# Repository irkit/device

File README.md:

IRKit Device
===

IRKit device and [IRKit SDK](https://github.com/irkit/ios-sdk) lets you control your home electronics from your iOS and Android devices.
IRKit device has a Infrared LED and receiver, and a WiFi module inside.
Internet connected devices can make IRKit send IR signals for you.

## Get IRKit Device

In Japan: [amazon.co.jp](http://www.amazon.co.jp/gp/product/B00H91KK26)  
World wide shipping available: [switch-science](https://international.switch-science.com/catalog/1644/)

## Schematics

Basically, it's a [Arduino Leonardo](http://arduino.cc/en/Main/ArduinoBoardLeonardo) fork with following modifications:

* added a [WiFi module](http://www.gainspan.com/gs1011mips) ( [GainSpan](http://www.gainspan.com/home) 's WiFi module ).
* added Infrared Receiver, Infrared LED and some LEDs.

## Firmware

It's basically a normal Arduino sketch.

See [IRKit.ino](https://github.com/irkit/device/blob/master/firmware/src/IRKit/IRKit.ino)

## Board

### Top

### Bottom

## Case

See [Case](https://github.com/irkit/device/tree/master/case)

## Extend it!

Following Arduino pins are pulled out for you.

* D2,D3,D4,D5,D12,TXLED
* A0,A1,A2,A3

See [IRKit.sch, eagle schematic file](https://github.com/irkit/device/blob/master/hardware/IRKit.sch) 's CN2

## How to update firmware

You can use [Arduino IDE](http://arduino.cc/en/Main/Software) to write IRKit's firmware.  
Follow this procedure (for MacOS).

1. Download, install and run [Arduino IDE](http://arduino.cc/en/Main/Software)
1. Connect IRKit using USB Micro-B cable to Mac.
1. Navigate to Arduino IDE Menu and select Tools -> Board -> "Arduino Leonardo".
1. Navigate to Arduino IDE Menu and select Tools -> Serial Port -> "/dev/tty.usbmodemXXXX".

   XXXX part should differ on your environment.

1. Download latest zip file from [IRKit device tags](https://github.com/irkit/device/releases).
1. Unzip it and open `firmware/src/IRKit/` directory.
1. Rename `version.template` to `version.c` .

   FYI. Product version is embedded here in official builds.

1. Double click `IRKit.ino` in the same directory.
1. Navigate to Arduino IDE Menu and click File -> Upload, to write into IRKit.
1. All Done!

### Example fork of IRKit firmware

[@acourreges](https://github.com/acourreges) created a branch [settings-led-cloud](https://github.com/acourreges/device/tree/settings-led-cloud/firmware) that enables you to configure:  
* Status LED behaviour (you might want to turn the LED off when the device is idle?)
* Enable/Disable cloud control (you might want IRKit not to connect to Internet?)

See [config.h](https://github.com/acourreges/device/blob/settings-led-cloud/firmware/src/IRKit/config.h) for details.

## How to get logs

IRKit logs what it's doing to USB serial, and you can use [Arduino IDE](http://arduino.cc/en/Main/Software) to see it.  
Follow this procedure (for MacOS).

1. Download, install and run [Arduino IDE](http://arduino.cc/en/Main/Software)
1. Connect IRKit using USB Micro-B cable to Mac.
1. Navigate to Arduino IDE Menu and select Tools -> Serial Port -> "/dev/tty.usbmodemXXXX".

   XXXX part should differ on your environment.

1. Navigate to Arduino IDE Menu and select Tools -> Serial Monitor.
1. Change new window's right-bottom settings to "No line ending" and "115200 baud", and close the window.
1. Reconnect IRKit and immediately start Serial Monitor again.

   This is to collect logs as soon as IRKit startups.

1. Copy and send logs to IRKit developer, thanks!

## ファームウェアアップデート方法

IRKitのファームウェアは、 [Arduino IDE](http://arduino.cc/en/Main/Software) を使って書き込むことができます。

出荷時のファームウェアバージョンによって、どのファームウェアバージョンまでアップデートできるかが変わります。  
以下の手順で現在のバージョンを確認し、対応するバージョンを使用してください。

| 現在のバージョン | 対応する最新のバージョン |
| --- | --- |
| 1.3.3以下 | [1.3.3](https://github.com/irkit/device/releases/tag/v1.3.3) |
| 1.3.4以上 | [最新](https://github.com/irkit/device/releases/latest) |

[IRKitシンプルリモコン](https://itunes.apple.com/us/app/irkit-simple-remote/id778790928?l=ja&ls=1&mt=8) を起動し、左上のボタンから設定画面を開くと、以下の画像の赤の四角のようにファームウェアバージョンを表示します。

以下がファームウェアのアップデート方法です(MacOS編)。

1. [Arduino IDE](http://arduino.cc/en/Main/Software) をダウンロードしてインストール後、起動します。
1. IRKitをUSB Micro-Bケーブルを使ってMacに接続します。
1. Arduino IDEのメニューから ツール -> マイコンボード -> "Arduino Leonardo" を選びます。
1. Arduino IDEのメニューから ツール -> シリアルポート -> "/dev/tty.usbmodemXXXX" を選びます。

   環境によってXXXXの部分やその前後が異なる場合があります。

1. ファームウェアをダウンロードし、zipファイルを解凍します。
1. 解凍したディレクトリ内にある `firmware/src/IRKit/` ディレクトリを開きます。
1. 同ディレクトリ内の `version.template` を `version.c` にリネームします。  

   参考) 製品版ではIRKitのバージョン情報をここに埋め込んでいます。

1. 同ディレクトリ内の `GSwifi.cpp` 内に埋め込んであるWi-Fiアクセスポイントのパスワードを書き換えます。  

   https://github.com/irkit/device/blob/master/firmware/src/IRKit/GSwifi.cpp#L1096  
   の `XXXXXXXXXX` を任意の文字列に書き換えてください。  
   参考) IRKitの出荷前に書き換えてから出荷しています。

1. 同ディレクトリ内の `IRKit.ino` をダブルクリックして Arduino IDE で開きます。
1. Arduino IDEのメニューから ファイル -> マイコンボードに書き込む を押してIRKitに書き込みます。
1. 完了！

### プログラムメモリについて

IRKitのマイコン ATmega32U4 はプログラムメモリを 32kB 積んでいますが、  
IRKitのファームウェアでそのほぼ全てを使用しています。

ファームウェアに改造を行い、機能追加する場合には、  
不必要な機能のログ出力や機能自体を削ってください。

[log.hの22-26行目](https://github.com/irkit/device/blob/master/firmware/src/IRKit/log.h#L22) 辺りをコメントアウトすることで、ログ出力を止めることができます。

### IRKitファームウェアのFork例

[@acourreges](https://github.com/acourreges)の[settings-led-cloud](https://github.com/acourreges/device/tree/settings-led-cloud/firmware)では、以下を変更可能にしています。  
* ステータスLEDの動作 (赤外線を送受信していない時にはLEDを消灯しておきたい??)
* クラウドとの接続を有効/無効 (IRKitをインターネットに接続せずに使いたい??)

詳しくは [config.h](https://github.com/acourreges/device/blob/settings-led-cloud/firmware/src/IRKit/config.h) を見てください。

[@shokai](https://github.com/shokai)の[tempe_sensor](https://github.com/shokai/irkit-device/compare/master...tempe_sensor)ブランチ、[sensors_json](https://github.com/shokai/irkit-device/compare/master...sensors_json)ブランチでは、  
温度センサからの入力、アナログピンの値を読み、IRKit内蔵のWebサーバからHTTP GETで取得できるようにしています。

詳しくは [IRKitのファームウェアを改造して温度センサーを追加した](http://shokai.org/blog/archives/8802) をご覧ください。

## ログ取得方法

IRKitは、USB Micro-Bを使いパソコンまたはMacに接続すると、動作ログを取得することができます。  
以下の手順でログを取得します(MacOS編)。

1. [Arduino IDE](http://arduino.cc/en/Main/Software) をダウンロードしてインストール後、起動します。
1. IRKitをUSB Micro-Bケーブルを使ってMacに接続します。
1. Arduino IDEのメニューから ツール -> シリアルポート -> "/dev/tty.usbmodemXXXX" を選びます。

   環境によってXXXXの部分やその前後が異なる場合があります。

1. Arduino IDEのメニューから ツール -> シリアルモニタ を選びます。
1. 新しく開いたウィンドウの右下の設定を "改行なし" "115200baud" に変更し、一度ウィンドウを閉じます。
1. IRKitのUSB Micro-Bケーブルを外し、再度接続した直後に、上記同様に シリアルモニタ を開きます。

   IRKit起動直後からのログを取得するためです。

1. ウィンドウに表示される文字列をコピーして開発者へメールしてください。ありがとうございます！

## License

Firmware is licensed under GPLv2 or later.  
See details in [firmware/LICENSE](https://github.com/irkit/device/blob/master/firmware/LICENSE).

Schematics are licensed under Creative Commons Attribution Share-Alike license.  
See details in [hardware/LICENSE](https://github.com/irkit/device/blob/master/hardware/LICENSE).

Case is licensed under Creative Commons Attribution NonCommercial Share-Alike license.  
See details in [case/LICENSE](https://github.com/irkit/device/blob/master/case/LICENSE).

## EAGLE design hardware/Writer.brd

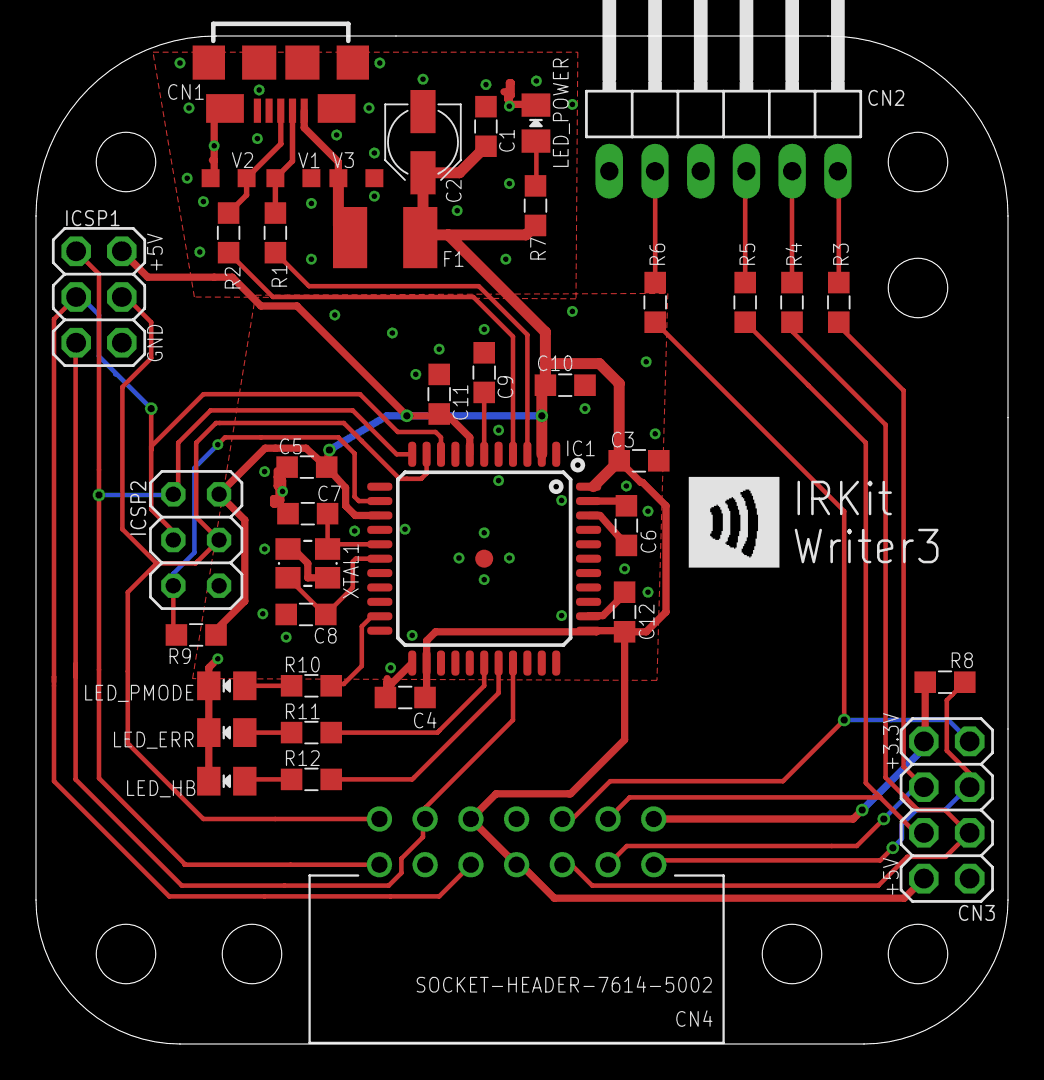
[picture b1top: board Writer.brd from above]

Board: 2 copper layers, 54.0 x 56.0 mm, 52 parts (0 on the bottom side), 33 nets.

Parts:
C1, C3, C4, C5, C6, C10, C11, C12: 0.1uF; SMD2012
C2: 10uF; PANASONIC_B
C7, C8: 12pF; SMD2012
C9: 1uF; SMD2012
CN1: ZX62-B-5PA(11); USB-MICROB
CN2: TTL-232R-3V3; 1X06/90
CN3: WiFi-Header; 2X04/D1.1
CN4: SOCKET-HEADER-7614-5002
F1: MF-MSMF075-2; L1812
IC1: ATMEGA32U4AU; TQFP44-PAD
ICSP1: IRKit ICSP; 2X03/D1.1
ICSP2: Writer ICSP; 2X03
LED_ERR: LED2012
LED_HB: LED2012
LED_PMODE: LED2012
LED_POWER: OSG50805C1C; LED2012
R1, R2: 22; SMD2012
R3, R4, R5, R6, R8: 1k; SMD2012
R7, R10, R11, R12: 5.1k; SMD2012
R9: 10k; SMD2012
SCREW1, SCREW2, SCREW3, SCREW4: flat-head M3 self-tapping; SCREW-M3
STANDOFF1, STANDOFF2, STANDOFF3, STANDOFF4, STANDOFF5, STANDOFF6, STANDOFF7: STAND-OFF
U$1: IRKIT-LOGO
V1, V2, V3: CG0603MLC-05E; CT/CN0603
XTAL1: 16MHz CL:10pF; CRYSTAL-3.2-2.5

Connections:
+3V3: CN3.1, CN4.2, R8.2
+5V: C1.1, C2.+, C3.2, C4.2, C5.2, C10.2, C11.2, C12.2, CN3.7, CN4.7, CN4.10, F1.2, IC1.2, IC1.7, IC1.14, IC1.24, IC1.34, IC1.44, ICSP1.2, ICSP2.2, R7.1, R9.2
AREF: C6.2, IC1.42
CTS#: CN2.2, R6.1
D1/LED_PMODE: IC1.21, R10.1
D8/LED_ERR: IC1.28, R11.1
D9/LED_HB: IC1.29, R12.1
GND: C1.2, C2.-, C3.1, C4.1, C5.1, C6.1, C7.1, C8.1, C9.1, C10.1, C11.1, C12.1, CN1.P5, CN1.S1, CN1.S2, CN1.S3, CN1.S4, CN1.S5, CN1.S6, CN2.1, CN3.8, CN4.8, CN4.11, IC1.5, IC1.15, IC1.23, IC1.35, IC1.43, IC1.P$1, ICSP1.6, ICSP2.6, LED_ERR.K, LED_HB.K, LED_PMODE.K, LED_POWER.K, V1.2, V2.2, V3.2, XTAL1.2, XTAL1.4
IRKIT/!RESET: CN4.12, IC1.30, ICSP1.5
IRKIT/MISO: CN4.13, IC1.11, ICSP1.1, ICSP2.1
IRKIT/MOSI: CN4.14, IC1.10, ICSP1.4, ICSP2.4
IRKIT/SCK: CN4.9, IC1.9, ICSP1.3, ICSP2.3
unnamed: LED_PMODE.A, R10.2
unnamed: LED_ERR.A, R11.2
unnamed: LED_POWER.A, R7.2
unnamed: LED_HB.A, R12.2
unnamed: CN1.P2, R1.2, V1.1
unnamed: CN1.P3, R2.2, V2.1
unnamed: CN1.P1, F1.1, V3.1
RTS#: CN2.6, R3.1
RXD: CN2.5, R4.1
TXD: CN2.4, R5.1
UCAP: C9.2, IC1.6
USB+: IC1.4, R2.1
USB-: IC1.3, R1.1
WIFI_UART0_CTS: CN3.3, CN4.3, R3.2
WIFI_UART0_RTS: CN3.2, CN4.6, R6.2
WIFI_UART0_RX: CN3.5, CN4.4, R5.2
WIFI_UART0_TX: CN3.6, CN4.5, R4.2
WIFI_UART1_RTS: CN3.4, CN4.1, R8.1
WRITER/!RESET: IC1.13, ICSP2.5, R9.1
XTAL1: C8.2, IC1.17, XTAL1.1
XTAL2: C7.2, IC1.16, XTAL1.3

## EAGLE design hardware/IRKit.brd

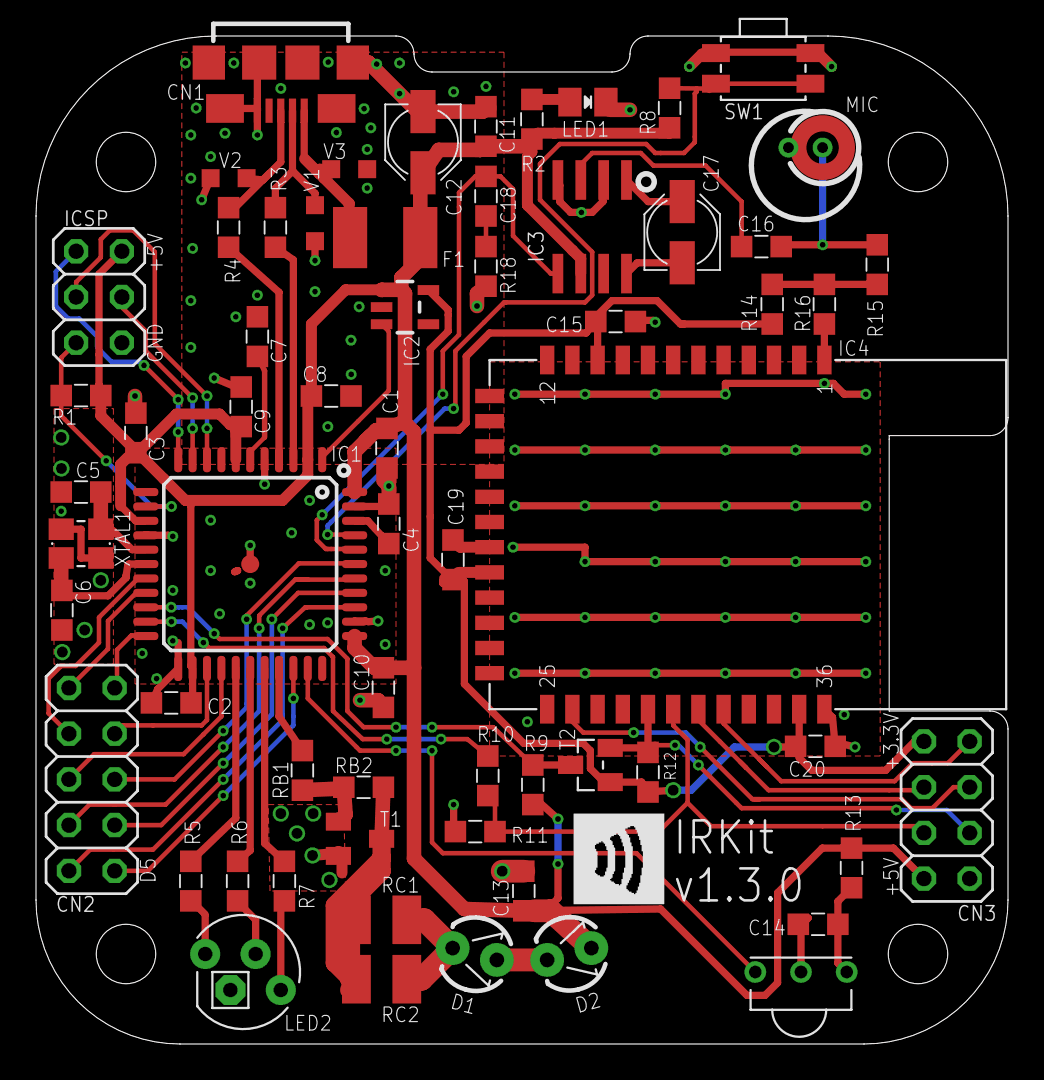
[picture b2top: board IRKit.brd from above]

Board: 2 copper layers, 54.0 x 56.0 mm, 75 parts (0 on the bottom side), 56 nets.

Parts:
C1, C2, C3, C4, C8, C9, C10, C11, C15, C19, C20: 0.1uF; SMD2012
C5, C6: 12pF; SMD2012
C7, C16: 1uF; SMD2012
C12, C17: 10uF; PANASONIC_B
C13, C14: 4.7uF; SMD2012
C18: 0.047uF; SMD2012
CN1: ZX62-B-5PA(11); USB-MICROB
CN2: 2X05
CN3: 2X04
D1, D2: VSLB3940; LED3MM
F1: MF-MSMF075-2; L1812
IC1: ATMEGA32U4AU; TQFP44-PAD
IC2: TLV70233DBVT; SOT23-5
IC3: LM386M-1/NOPB; SO08
IC4: GS1011MXXS
ICSP: ICSP; 2X03
IR-RECEIVER: PL-IRM2161; IR-RECEIVER
LED1: PG1112H-TR; LED2012
LED2: 5MMRGBLED; LED5MMRGB
LEDCAP1: LED-CAP
MIC: 254-ECM6044-RO; MIC_SMD_4MM
R1, R9: 10k; SMD2012
R2, R6, R10, R15: 2.2k; SMD2012
R3, R4: 22; SMD2012
R5, R7, R11, R14: 3.3k; SMD2012
R8, R16: 5.1k; SMD2012
R12: 4.7k; SMD2012
R13: 220; SMD2012
R18: 10; SMD2012
RB1: 1.8k; SMD2012
RB2: 10k; SMD2012
RC1, RC2: 10Ω 0.5W; 3225
SCREW1, SCREW2, SCREW3, SCREW4: flat-head M3 self-tapping; SCREW-M3
SP1, SP2: LK-5; LED-SPACER-LK
STANDOFF1, STANDOFF2, STANDOFF3, STANDOFF4: STAND-OFF
SW1: EVQPUJ02K; TACTILE-SWITCH-EVQPUJ02K
T1: 2SD1781KT146Q; SC59-BEC
T2: BSS138; SOT23
U$1: IRKIT-LOGO
V1, V2, V3: CG0603MLC-05E; CT/CN0603
XTAL1: 16MHz CL:10pF; CRYSTAL-3.2-2.5

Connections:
!RESET: IC1.13, ICSP.5, R1.1
+2V: R14.1, R15.2, R16.2
+3V3: C15.2, C19.2, C20.2, CN3.1, IC2.5, IC4.10, IC4.20, IC4.35, R12.2, R14.2, T2.1
+5V: C1.2, C2.2, C3.2, C8.2, C9.2, C10.2, C11.1, C12.+, C13.1, CN3.7, D2.A, F1.2, IC1.2, IC1.7, IC1.14, IC1.24, IC1.34, IC1.44, IC2.1, IC3.6, ICSP.2, R1.2, R2.1, R8.1, R9.2, R13.2
A0: CN2.9, IC1.36
A1: CN2.8, IC1.37
A2: CN2.7, IC1.38
A3: CN2.6, IC1.39
A4/MIC: C18.1, IC1.40, IC3.5
A5/!RESET_SWITCH: IC1.41, R8.2, SW1.1, SW1.3
AREF: C4.2, IC1.42
D0/WIFIRX: IC1.20, R9.1, T2.3
D1/WIFITX: IC1.21, R10.2
D2: CN2.1, IC1.19
D3: CN2.3, IC1.18
D4: CN2.4, IC1.25
D5: CN2.10, IC1.31
D6/LED_R: IC1.27, R5.1
D7/LDO3.3_EN: IC1.1, IC2.3
D8/LED_B: IC1.28, R6.1
D9/LED_G: IC1.29, R7.1
D10/IROUT: IC1.30, RB1.2
D12: CN2.5, IC1.26
D13/IRIN: IC1.32, IR-RECEIVER.1
GND: C1.1, C2.1, C3.1, C4.1, C5.1, C6.1, C7.1, C8.1, C9.1, C10.1, C11.2, C12.-, C13.2, C14.2, C15.1, C19.1, C20.1, CN1.P5, CN1.S1, CN1.S2, CN1.S3, CN1.S4, CN1.S5, CN1.S6, CN3.8, IC1.5, IC1.15, IC1.23, IC1.35, IC1.43, IC1.P$1, IC2.2, IC3.2, IC3.4, IC4.1, IC4.19, IC4.36, ICSP.6, IR-RECEIVER.2, LED1.K, LED2.3, MIC.2, R11.1, R16.1, R18.2, SW1.2, SW1.4, T1.E, V1.2, V2.2, V3.2, XTAL1.2, XTAL1.4
IRLED: D1.K, RC1.2, RC2.2
MICOUT: C16.1, MIC.1, R15.1
MISO: IC1.11, ICSP.1
MOSI: IC1.10, ICSP.4
unnamed: C17.-, IC3.8
unnamed: LED1.A, R2.2
unnamed: C16.2, IC3.3
unnamed: LED2.1, R7.2
unnamed: C17.+, IC3.1
unnamed: RB1.1, RB2.1, T1.B
unnamed: RB2.2, RC1.1, RC2.1, T1.C
unnamed: C18.2, R18.1
unnamed: C14.1, IR-RECEIVER.3, R13.1
unnamed: LED2.2, R6.2
unnamed: LED2.4, R5.2
unnamed: CN1.P2, R3.2, V1.1
unnamed: CN1.P3, R4.2, V2.1
unnamed: CN1.P1, F1.1, V3.1
unnamed: D1.A, D2.K
SCK: IC1.9, ICSP.3
TXLED: CN2.2, IC1.22
UCAP: C7.2, IC1.6
USB+: IC1.4, R4.1
USB-: IC1.3, R3.1
WIFI_UART0_CTS: CN3.3, IC4.31
WIFI_UART0_RTS: CN3.2, IC4.32
WIFI_UART0_RX: CN3.5, IC4.30, R10.1, R11.2
WIFI_UART0_TX: CN3.6, IC4.29, R12.1, T2.2
WIFI_UART1_RTS: CN3.4, IC4.26
XTAL1: C6.2, IC1.17, XTAL1.1
XTAL2: C5.2, IC1.16, XTAL1.3

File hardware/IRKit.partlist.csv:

"Qty";"Value";"Device";"Package";"Parts";"Description";"";
"1";"";"PINHD-2X4";"2X04";"CN3";"PIN HEADER";"";
"1";"";"PINHD-2X5";"2X05";"CN2";"PIN HEADER";"";
"1";"0.047uF";"CAPACITOR2012";"SMD2012";"C18";"Generic Capacitor";"";
"11";"0.1uF";"CAPACITOR2012";"SMD2012";"C1, C2, C3, C4, C8, C9, C10, C11, C15, C19, C20";"Generic Capacitor";"";
"1";"1.8k";"RESISTOR-US2012";"SMD2012";"RB1";"Generic Registor";"";
"1";"10";"RESISTOR-US2012";"SMD2012";"R18";"Generic Registor";"";
"3";"10k";"RESISTOR-US2012";"SMD2012";"R1, R9, RB2";"Generic Registor";"";
"2";"10uF";"CAPACITOR-POLPANASONIC_B";"PANASONIC_B";"C12, C17";"Generic Capacitor with Polarity";"";
"2";"10Ω 0.5W";"R3225";"3225";"RC1, RC2";"RESISTOR";"";
"2";"12pF";"CAPACITOR2012";"SMD2012";"C5, C6";"Generic Capacitor";"";
"1";"16MHz CL:10pF";"CRYSTAL-3.2-2.5";"CRYSTAL-3.2-2.5";"XTAL1";"";"";
"2";"1uF";"CAPACITOR2012";"SMD2012";"C7, C16";"Generic Capacitor";"";
"4";"2.2k";"RESISTOR-US2012";"SMD2012";"R2, R6, R10, R15";"Generic Registor";"";
"2";"22";"RESISTOR-US2012";"SMD2012";"R3, R4";"Generic Registor";"";
"1";"220";"RESISTOR-US2012";"SMD2012";"R13";"Generic Registor";"";
"1";"254-ECM6044-RO";"MICELECTRET_SMD";"MIC_SMD_4MM";"MIC";"Omni-directional electret condenser microphone.";"";
"1";"2SD1781KT146Q";"MMUN2211LT1-NPN-SC59-BEC";"SC59-BEC";"T1";"NPN Transistror";"";
"4";"3.3k";"RESISTOR-US2012";"SMD2012";"R5, R7, R11, R14";"Generic Registor";"";
"1";"4.7k";"RESISTOR-US2012";"SMD2012";"R12";"Generic Registor";"";
"2";"4.7uF";"CAPACITOR2012";"SMD2012";"C13, C14";"Generic Capacitor";"";
"2";"5.1k";"RESISTOR-US2012";"SMD2012";"R8, R16";"Generic Registor";"";
"1";"5MMRGBLED";"5MMRGBLED";"LED5MMRGB";"LED2";"";"";
"1";"ATMEGA32U4AU";"ATMEGA32U4AU";"TQFP44-PAD";"IC1";"";"";
"1";"BSS138";"BSS138";"SOT23";"T2";"";"";
"3";"CG0603MLC-05E";"VARISTORCN0603";"CT/CN0603";"V1, V2, V3";"VARISTOR";"";
"1";"EVQPUJ02K";"TACTILE-SWITCHEVQPUJ02K";"TACTILE-SWITCH-EVQPUJ02K";"SW1";"TACTILE SWITCH";"";
"1";"GS1011MXXS";"GS1011MXXS";"GS1011MXXS";"IC4";"";"";
"1";"ICSP";"PINHD-2X3";"2X03";"ICSP";"PIN HEADER";"";
"1";"LED-CAP";"LED-CAP";"LED-CAP";"LEDCAP1";"";"";
"2";"LK-5";"LED-SPACER-LK";"LED-SPACER-LK";"SP1, SP2";"";"";
"1";"LM386M-1/NOPB";"LM386M-1";"SO08";"IC3";"Low Voltage Audio Power Amplifier";"";
"1";"MF-MSMF075-2";"L-EUL1812";"L1812";"F1";"INDUCTOR, European symbol";"";
"1";"PG1112H-TR";"LED-2012";"LED2012";"LED1";"Through-hole LED";"";
"1";"PL-IRM2161";"PL-IRM2161";"IR-RECEIVER";"IR-RECEIVER";"PL-IRM2161-XD1";"";
"4";"STAND-OFF";"STAND-OFF";"STAND-OFF";"STANDOFF1, STANDOFF2, STANDOFF3, STANDOFF4";"#4 Stand Off";"";
"1";"TLV70233DBVT";"TLV702XXSMD";"SOT23-5";"IC2";"TLV702xx";"";
"2";"VSLB3940";"LED-3MM";"LED3MM";"D1, D2";"Through-hole LED";"";
"1";"ZX62-B-5PA(11)";"USB-CONNECTORMICROB";"USB-MICROB";"CN1";"";"";
"4";"flat-head M3 self-tapping";"SCREW";"SCREW-M3";"SCREW1, SCREW2, SCREW3, SCREW4";"";"";

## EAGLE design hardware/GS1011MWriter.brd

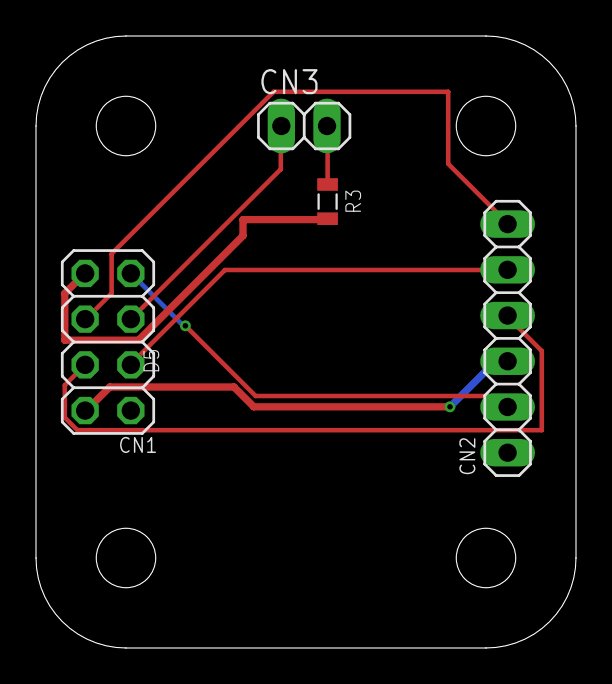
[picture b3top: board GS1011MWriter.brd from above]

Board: 2 copper layers, 30.0 x 34.0 mm, 8 parts (0 on the bottom side), 9 nets.

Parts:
CN1: 2X04
CN2: 1X06
CN3: 1X02
R3: 10k; 2012
STANDOFF1, STANDOFF2, STANDOFF3, STANDOFF4: STAND-OFF

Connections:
+3V3: CN1.1, R3.2
+5V: CN1.7, CN2.3
GND: CN1.8, CN2.1
unnamed: CN3.2, R3.1
WIFI_UART0_CTS: CN1.3, CN2.6
WIFI_UART0_RTS: CN1.2, CN2.2
WIFI_UART0_RX: CN1.5, CN2.4
WIFI_UART0_TX: CN1.6, CN2.5
WIFI_UART1_RTS: CN1.4, CN3.1

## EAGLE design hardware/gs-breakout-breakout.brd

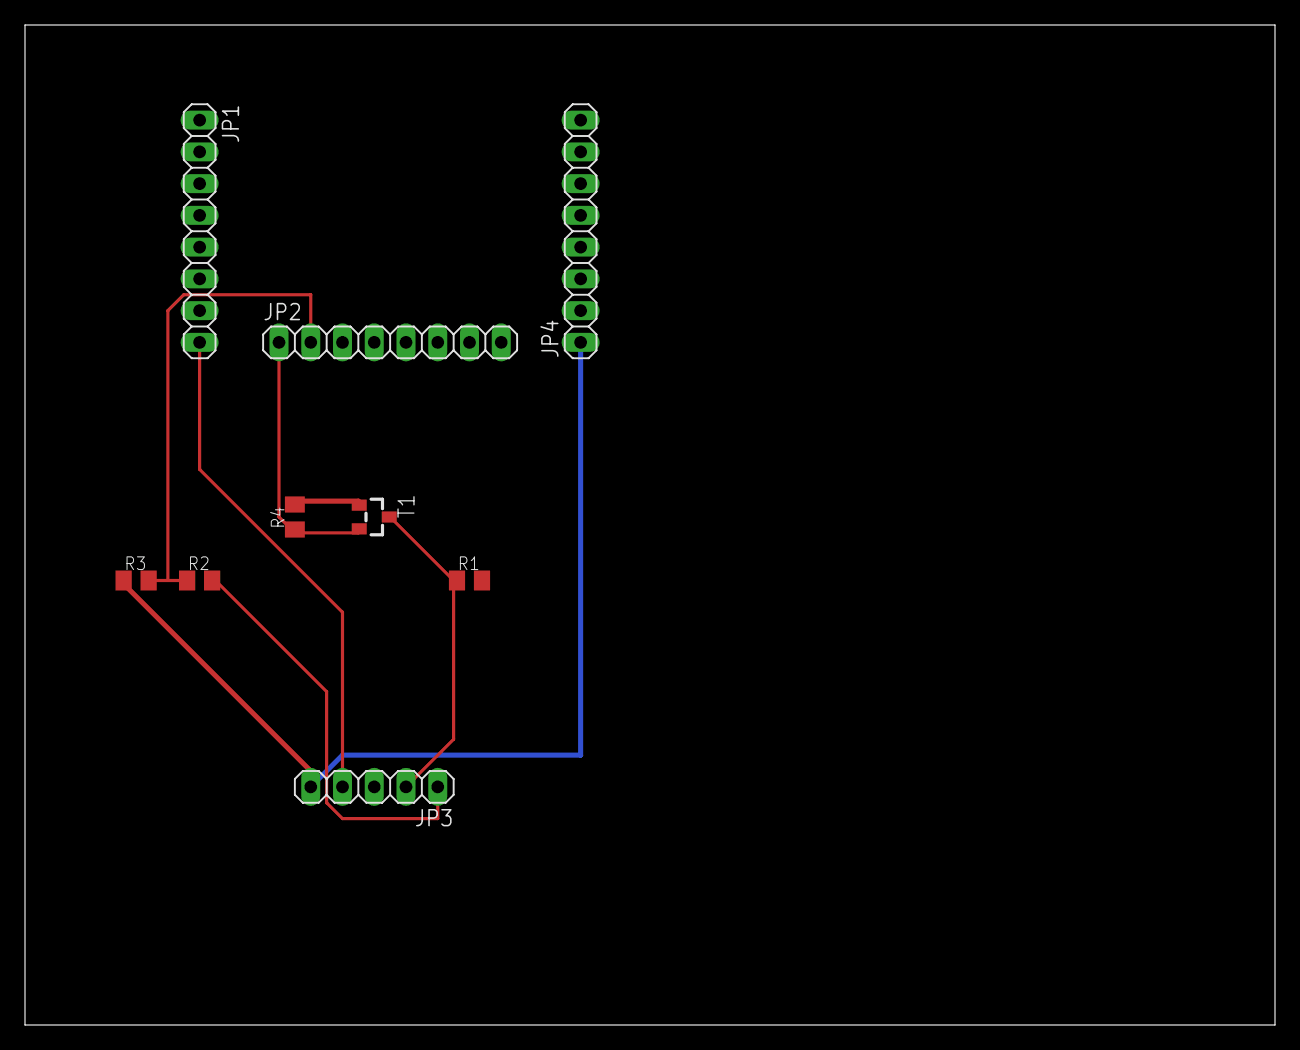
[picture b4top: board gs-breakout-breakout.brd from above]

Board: 2 copper layers, 100.0 x 80.0 mm, 9 parts (0 on the bottom side), 7 nets.

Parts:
JP1, JP2, JP4: 1X08
JP3: 1X05
R1: 10k; SMD2012
R2: 2.2k; SMD2012
R3: 3.3k; SMD2012
R4: 4.7k; SMD2012
T1: BSS138; SOT23

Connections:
+3V3: R4.2, T1.1
D0/RX: JP3.2, R1.1, T1.3
D1/TX: JP3.1, R2.2
GND: JP3.5, JP4.1, R3.1
V3_3: JP1.8, JP3.4
WIFI_UART0_RX: JP2.2, R2.1, R3.2
WIFI_UART0_TX: JP2.1, R4.1, T1.2

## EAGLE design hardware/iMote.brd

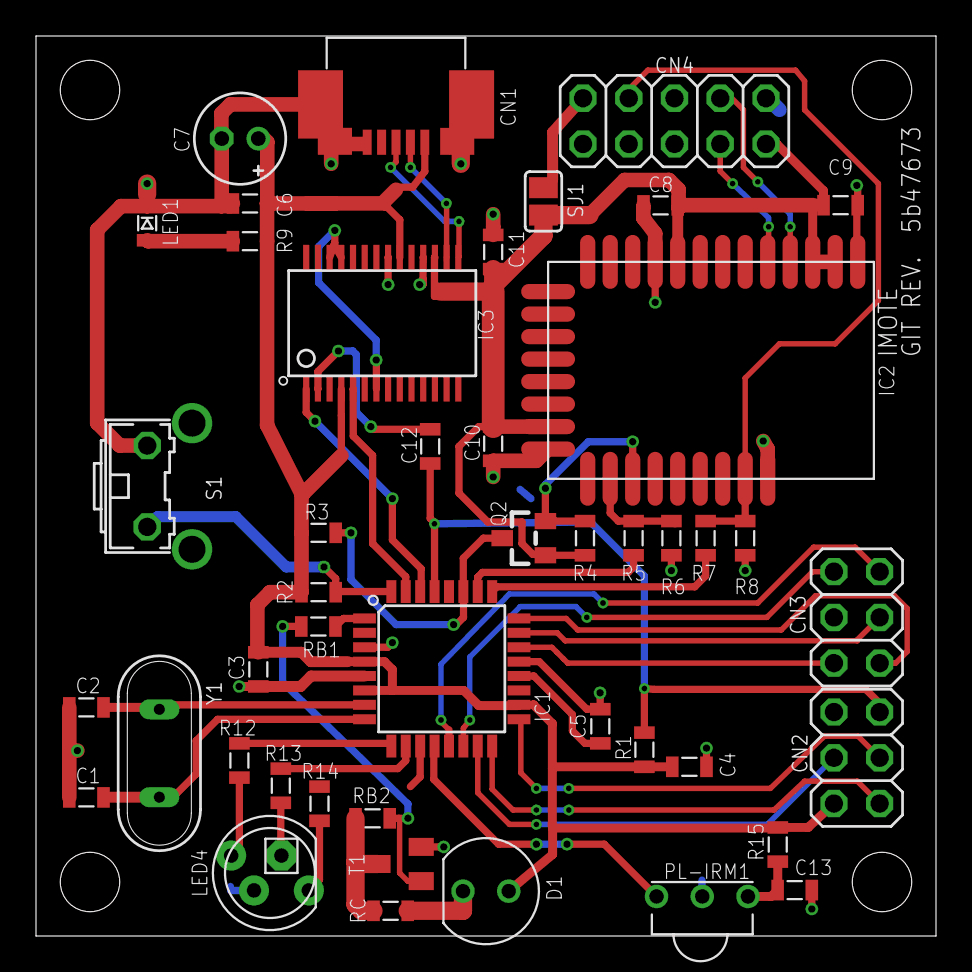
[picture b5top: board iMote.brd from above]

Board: 2 copper layers, 50.0 x 50.0 mm, 50 parts (0 on the bottom side), 43 nets.

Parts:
C1, C2: 22pF; 2012
C3, C4, C5, C6, C8, C9, C10, C11, C12: 0.1uF; 2012
C7: 10uF; E2-5
C13: 4.7uF; 2012
CN1: USB-MINIB-UX60SC-MB
CN2: ICSP; 2X03
CN3: PIN_Header; 2X03
CN4: CC-HEADER; 2X05
D1: VSLB3940; LED-3MM
IC1: ATmega328P-AU; TQFP32-08
IC2: BLE112-A-VISUAL; BLE112-A
IC3: FT232RLSSOP; SSOP28DB
LED1: 5V; LED-2012
LED4: 5MMRGBLED; LED5MMRGB
PL-IRM1: PL-IRM2161; IR-RECEIVER
Q2: BSS138; SOT23
R1: 10K; 2012
R2: 1K; 2012
R3: 10k; 2012
R4: 4.7k; 2012
R5, R7: 2.2k; 2012
R6, R8: 3.3k; 2012
R9: 220; 2012
R12: 1.2K; 2012
R13: 2.4k; 2012
R14: 1k; 2012
R15: 200; 2012
RB1: 4.7k; 2012
RB2: 10k; 2012
RC: 47; 2012
S1: S1; B3F-31XX
SJ1: 0; SJ
STANDOFF1, STANDOFF2, STANDOFF3, STANDOFF4: STAND-OFF
T1: 2SD1718; SC59-BEC
U$1: 5b47673; GIT-REVISION
Y1: 16MHz; XTAL-HC-49/S

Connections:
!BLE/RST: CN4.7, IC2.RESET, R7.1, R8.2
!RESET: C12.2, CN2.5, IC1.29, R1.1
+3V3: C8.1, C9.1, C10.1, C11.1, CN4.2, IC2.AVDD, IC2.AVDD@2, IC2.DVDD, IC2.VDD_USB, IC3.17, Q2.1, R4.2, SJ1.2
+5V: C3.2, C4.2, C6.1, C7.+, CN1.VBUS, CN2.2, D1.A, IC1.4, IC1.6, IC1.18, IC3.4, IC3.20, R1.2, R2.2, R3.2, R9.1, R15.2
A0: CN3.4, IC1.23
A1: CN3.6, IC1.24
A2/RST_HV: IC1.25, R7.2
A3/TX_HV: IC1.26, R5.2
A4/RX_HV: IC1.27, Q2.3, R3.1
A7: CN3.5, IC1.22
AREF: C5.2, IC1.20
BLE/P2_1: CN4.4, IC2.P2_1
BLE/P2_2: CN4.3, IC2.P2_2
D0/USBRX: IC1.30, IC3.1
D1/USBTX: IC1.31, IC3.5
D2/BTN: IC1.32, R2.1, S1.2
D3/IROUT: IC1.1, RB1.2
D5/LED_R: IC1.9, R12.1
D6/LED_G: IC1.10, R13.1
D7/LED_B: IC1.11, R14.1
D8/IRIN: IC1.12, PL-IRM1.1
D9: CN3.2, IC1.13
D10: CN3.1, IC1.14
D11/MOSI: CN2.4, IC1.15
D12/MISO: CN2.1, IC1.16
D13/SCK: CN2.3, IC1.17
GND: C1.1, C2.1, C3.1, C4.1, C5.1, C6.2, C7.-, C8.2, C9.2, C10.2, C11.2, C13.2, CN1.GND, CN1.S$1, CN1.S$1@2, CN1.S$1@3, CN1.S$2, CN1.S$2@2, CN1.S$2@3, CN2.6, CN3.3, CN4.1, IC1.3, IC1.5, IC1.21, IC2.GND, IC2.GND@2, IC2.GND@3, IC2.GND@4, IC3.7, IC3.18, IC3.21, IC3.25, IC3.26, LED1.C, LED4.3, PL-IRM1.2, R6.1, R8.1, S1.1, T1.E
IRLED: D1.C, RC.2
unnamed: C1.2, IC1.8, Y1.1
unnamed: C2.2, IC1.7, Y1.2
unnamed: LED1.A, R9.2
unnamed: LED4.4, R12.2
unnamed: C12.1, IC3.2
unnamed: RB1.1, RB2.1, T1.B
unnamed: RB2.2, RC.1, T1.C
unnamed: LED4.2, R13.2
unnamed: C13.1, PL-IRM1.3, R15.1
unnamed: LED4.1, R14.2
PRG/VDD: CN4.9, SJ1.1
RX_LV/BLERX: IC2.P0_5, R5.1, R6.2
TX_LV/BLETX: IC2.P0_4, Q2.2, R4.1
USBD+: CN1.D+, IC3.15
USBD-: CN1.D-, IC3.16

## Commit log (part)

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2013-11-01 fixed DRC errors around MIC fatter lines around IR LED
2013-11-01 resolve ip address before HTTP request
2013-11-01 close CID after each request from us this (probably) prevents CID overflow
2013-11-01 enable mDNS and reduce program memory for it...
2013-11-05 move hidden guides to dimension layer
2013-11-05 make lines around T1 thinner, because it took long to warm T1's emitter pad move R1 a little bit far from ICSP header, not to conflict with it
2013-11-05 added screws updated microphone input resistor value 2k -> 2.2k change voltage dividing resistors values 2k/3.3k -> 3.3k/5.1k
2013-11-06 make drill more thicker for IR receiver, because it was not easy enough to insert. make GND plane's line width thiner, to make IR receiver's thermal thinner (it was hard to warm up)
2013-11-06 use "irkit" model (boards.txt not included) to set vid,bid
2013-11-06 added "POST /keys" route, which adds another key to our door and returns it
2013-11-07 morse to keys works!
2013-11-08 added IRKit writer
2013-11-08 if we encounter morse error, error continues til "word" end
2013-11-08 make microphone 4mm/6mm compatible pattern
2013-11-08 added more dimension
2013-11-09 moved some lines to guide layer
2013-11-09 add TCP keepalive (other lines are to slim program memory)
2013-11-10 refactored
2013-11-11 IR recv timeout uses counter/timer ISR
2013-11-11 ignore IR noise
2013-11-11 naming conventions
2013-11-11 when we've received response from server, set clientRequest.cid to undefined, before we close connection, because close(cid) waits for response from server, and that might include something we don't 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
2013-11-11 naming convention
2013-11-11 hardware reset if any error occurs
2013-11-11 use drill 0.9 to use conthrough(?)
2013-11-11 move silk inside our board :(
2013-11-11 more space
2013-11-11 move bss138 to my.lbr
2013-11-11 TCP_KEEPALIVE revival, wish this fixes bug that GS often turns into this error state which GS responds with ERROR only
2013-11-11 long press button and clear wifi, key credentials
2013-11-11 allow cross domain access
2013-11-11 ignore <ESC>O, <ESC>F responses, because they mix up in other <ESC> bulk data transfers, and have no actual merit to parse
2013-11-12 remember response handlers for each cid, so that we can handle multiple clientRequest's responses
2013-11-12 we might be out of memory, delay execution of POST /keys to server, til next tick so that we get clean stack
2013-11-12 script to benchmark our embedded web server (non parallel though..)
2013-11-12 change baud rate to 38400, 57600 causes data loss while I want to debug using Serial.print . we might want to re-implement Serial.write to use GS's software flow control, to maximize speed
2013-11-12 shorter, but enough debug lines
2013-11-13 give ringbuffer it's buffer from outside, and protect over put-ing
2013-11-13 make a ringbuffer to delay commands to next loop
2013-11-13 refactoring
2013-11-14 ignore Rhino exported file types
2013-11-14 make ir test work
2013-11-14 shrinking program memory
2013-11-16 make everything a single poly surface
2013-11-16 successfully handle long(over 1500bytes) messages, by remembering Content-Length for each POST requests and responses
2013-11-16 less program memory
2013-11-19 script to generate "IR_put(xxx);" and JSON data
2013-11-19 pack/unpack works
2013-11-19 save tree table in EEPROM to save program memory
2013-11-20 less program memory 28368
2013-11-20 make packer test work again on mac
2013-11-21 script to easily test pack/unpack
2013-11-21 fix test
2013-11-22 move IR_get after setting timer register, to not affect timer accuracy this works!!!!
2013-11-22 use cycles after enabling timer
2013-11-22 refactored to compress program memory
2013-11-22 fix bug that ring buffer continues to be full when server responds with non 200 response
2013-11-22 moving to _irkit._tcp
2013-11-24 moved to api.getirkit.com
2013-11-25 builds fine
2013-11-25 HardwareSerialX is equal to HardwareSerial using our RingBuffer
2013-11-25 increase global buffer size(= IR buffer size) and uint8_t -> uint16_t to be able to consume fablabkamakura's air conditioners signal (363bytes)
2013-11-25 refactoring to reduce SRAM usage
2013-11-26 HTTP response includes Server header with IRKit's version
2013-11-26 SW2's pin4 wasn't connected to GND
2013-11-27 added IR LED shape
2013-11-28 replaced LED spacer to LK series package
2013-11-28 mic part no changed to KUB2823
2013-11-28 placed guide for text, dimension for IR hole
2013-11-29 clear doesnt implicitly save, explicitly call save when you need to
2013-11-29 disable morse while trying to connect (avoid connecting while connecting)
2013-11-29 since 2.5.1, cid is not re-used immediately, so it reaches a-f easily. treat cid as ASCII in commands
2013-11-29 use less SRAM
2013-11-29 we might want to transfer more in the future (like static IP), so prepare reserved state future iOS and firmware can support more parameters, while still supporting old firmware
2013-11-29 added guide for more text
2013-12-02 fixed dimension
2013-12-03 hand command mode
2013-12-03 useful for debugging
2013-12-07 log on receive timeout
2013-12-09 key -> devicekey
2013-12-09 remove unused
2013-12-09 suspend gs.close and startNormalOperation to next loop, to avoid GS from resetting, but no help
2013-12-10 name -> hostname for explicity
2013-12-10 more
2013-12-10 suspend close to next loop
2013-12-12 avoid empty body 400 requests
2013-12-13 fix bug that we started receiving IR data while transferring it to server
2013-12-13 test script for base64 encode, unpack
2013-12-13 clear route_count_ on reset
2013-12-13 comment out in GSwifi.cpp if you want less program memory
2013-12-14 more customizable
2013-12-14 fix base64 encoder bug
2013-12-16 case for factory jig
2013-12-17 fix test program
2013-12-17 oooooooooops
2013-12-17 moved things around
2013-12-17 removed IRKit.{cpp,h} , it's useless and not make things easy for hackers removed global.buffer_mode , it's just a flag for debugging, not making debugging easier
2013-12-17 remove unused dependency
2013-12-18 naming, moving things around
2013-12-20 changes for factory
2013-12-23 disable TCP_MAXRT and TCP_KEEPALIVE_X, because these commands takes some time to issue, and GS1011MIPS denies short TCP_KEEPALIVE_INTVL, and our server (currently Heroku) disconnects connections afte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
2013-12-23 don't wait
2013-12-23 fix irpacker_unpack_sequence for debugging
2013-12-23 explicitly set non global as static
2013-12-23 c -> cpp for debuggability (.c can't use Serial.print)
2013-12-24 fix ir-tester
2013-12-24 debug easy
2013-12-26 we have some space to enable dump
2013-12-26 GET /messages resurrected
2013-12-26 less program memory and refactoring
2013-12-26 suspend GET /m after receiving GET /messages request
2013-12-26 better error handling, colorled shouldn't show blue(ok) when not connected
2013-12-26 make long button reset work faster
2013-12-27 adjust for new case
2013-12-29 blink only when device POSTs to server
2013-12-30 removed trash
2014-01-03 start limitedAP mode at the same time with morse enabled. POST /wifi receives the same thing as morse does.
2014-01-04 switch off logs to make program memory space
2014-01-05 we limit wifi power when using limitedap mode because of open security, so set power back to normal when joining infrastructure wifi
2014-01-05 clear keys before receiving POST /wifi body
2014-01-06 we have space for molog
2014-01-06 yellow blink when morse is proceeding
2014-01-11 rename
2014-01-14 added license
2014-01-19 don't setupMDNS if not listening, setupMDNS just does sends some commands, but all just fails
2014-01-20 refactor
2014-01-20 GS software reset didn't work when we encountered "ERROR: SOCKET FAILURE 0" see https://gist.github.com/mash/080bd869d5bd10e90df5
2014-01-20 let go earlier
2014-01-20 oops, comments
2014-01-20 program memory..
2014-01-20 short IR probably be noise reduce POST /p to internet server, to make IRKit more stable and internet server more light
2014-01-21 small fix re-render images
2014-01-27 added license in readme changed case license to non-commericial, don't want IRKit users to be confused seeing very similar products
2014-01-27 can't see log anyway
2014-01-27 wrote about logging
2014-01-30 script to create github releases
2014-02-06 this style is more useful to make json
2014-02-11 reduce program memory
2014-02-13 don't allow code < '0' too
2014-02-19 fix led test firmware
2014-02-19 integrate rows if device and value is same
2014-02-19 follow sch,brd updates
2014-02-23 store in Flash
2014-02-23 fix bug that POST body wasn't sent
2014-02-23 just write explicitly
2014-02-23 add functions to save and load wep key to eeprom
2014-02-24 fix gainspan test
2014-02-25 tester doesn't do dnslookup, https
2014-02-25 fix bug that tries to call unexisting callback
2014-03-13 disable dhcp server after stopping limitedAP and before starting joining infrastructure
2014-03-13 don't update without prompt
2014-03-13 changed LED part no. to what I can buy in reel packaging
2014-03-13 ran Seeed's gerber generator
2014-03-17 enable logs again, removing morse made some space
2014-03-18 delay turning blue til POST /d succeeds
2014-03-28 minimal code to save limitedAP password into EEPROM
2014-03-31 define missing "SAVE_IRPACKER_TREE" in initialize-eeprom #1
2014-04-02 Turn ON blue LED when wifi connected
2014-04-04 added LED for ArduinoISP PMODE,ERR,HB. make ISP work on ATMEGA32U4.
2014-04-04 why is this here?
2014-04-09 define another command to delay calling POST /d , to avoid deepening and overflowing stack
2014-04-11 reset to initial state fter POST /d failed
2014-04-28 wrote about how to check firmware version and updating version is limited to firmware version
2014-04-28 wrote about program memory, and remove logging
2014-05-08 When client request timeout happens, it takes a long time to wait til GS fixes it's own state. Let's not wait for it and just reset, to make ourself simpler.
2014-05-12 Ignore whole IR signal if any of it's interval between rising/falling edges are shorter than threshold.
2014-05-21 restore IR_reset, it's used in factorychecker
2014-06-02 fix bug which update fails when there's no rows
2014-07-23 Use ghq
2014-07-24 Use GS1011MEPS like GS1011MIPS
2014-08-19 Makefile to create .lst files
2014-08-20 Move limited AP password to Flash
2014-08-27 Use less SRAM (stack) in GSwifi::request
2014-08-27 close on next loop to avoid recursively calling ::command
2014-08-27 Delay setregdomain to next loop, to avoid recursive call of command()
2014-08-27 Move big buffer to static, to avoid stack overflow. parseLine is not called recursively, so making buf static is safe.
2014-08-31 HTTP requests use some amount of stack memory, so only request sequentially.
2014-11-25 Fixed spec
2014-11-26 Wrote documents about IrCtrl
2014-11-26 More docs
2015-01-12 Added options to customize the LED behavior and enable/disable cloud control, through config.h.
2015-02-08 Cut SRAM usage by 6 bytes.
2015-03-07 Android app availble, international.switch-science.com, no microphone
2015-04-16 use Arduino-1.0.5 for less SRAM usage; see https://github.com/irkit/device/issues/9#issuecomment-89983746
2015-07-20 Update spec
2015-07-23 Another test case to check if number presentation of password works
2015-07-23 Test passes
2015-07-23 Require X-Requested-With header to exist when responding to http request.
2015-07-23 Remove unused logs to open up ram
2015-07-23 Disable logs for production
2015-07-27 Insert marker for password replacer

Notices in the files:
parts and their libraries:
m-pad-2.1: License : GNU General Public License version 2 (see bottom)
SparkFun-Electromechanical: Licensing: CC v3.0 Share-Alike You are welcome to use this library for commercial purposes.
